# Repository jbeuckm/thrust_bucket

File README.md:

## Atmega328 test stand for rocket motors.

Based on the ["Ultra Simple Bucket Stand"](http://aeroconsystems.com/cart/test-stand-pictorial)

* Rotary Encoder + button + LCD interface
* reads HX711 interface for load cell tracking at 80hz
* writes force readings to SD card
* beeper to signal countdown
* FET to light the igniter

2/19/17 Motor holder bolted on

2/9/17 Status: Loadcell Mounted on I-Beam

### Dependencies

LCD library:
[https://github.com/adafruit/Adafruit-RGB-LCD-Shield-Library](https://github.com/adafruit/Adafruit-RGB-LCD-Shield-Library)

HX711:
[https://github.com/bogde/HX711](https://github.com/bogde/HX711)

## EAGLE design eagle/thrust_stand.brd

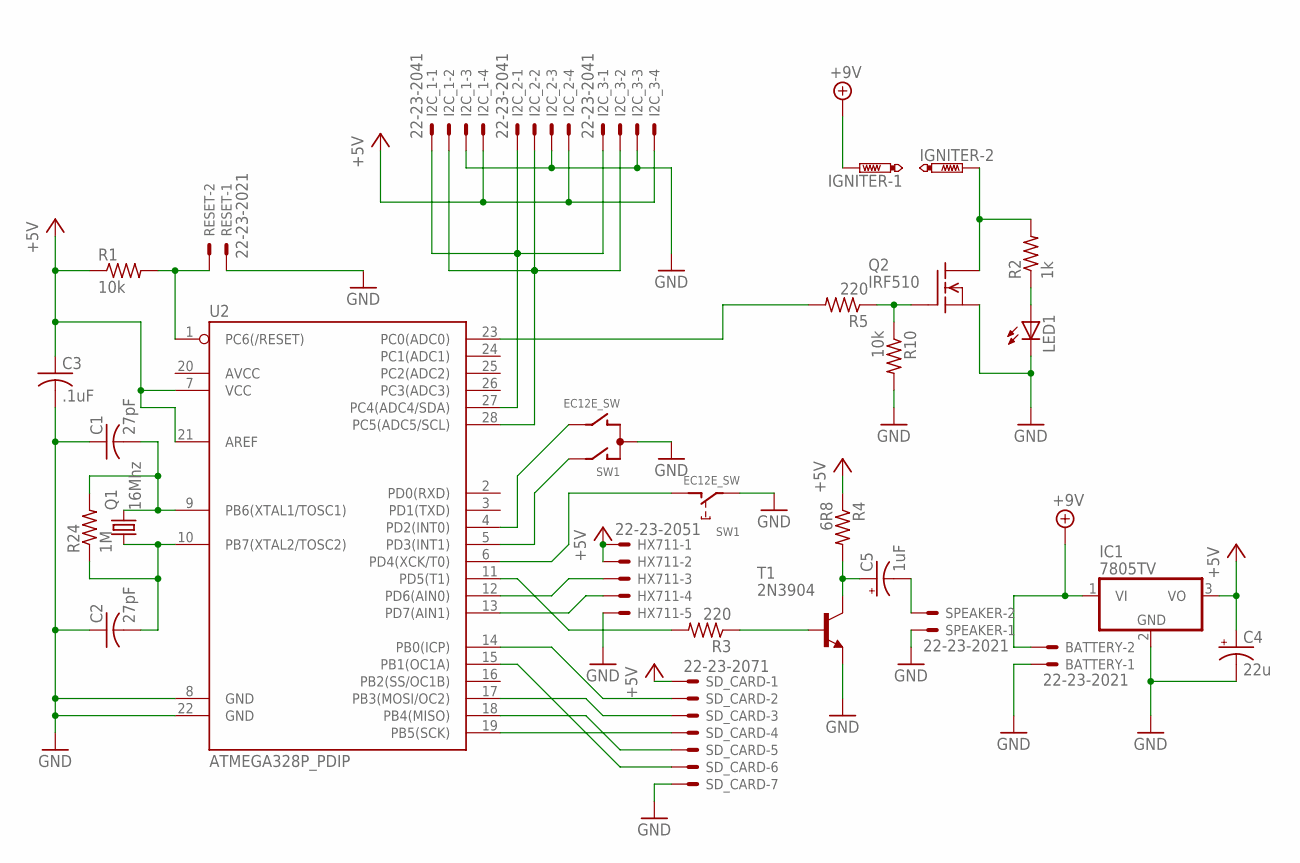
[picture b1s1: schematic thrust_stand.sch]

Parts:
BATTERY: 22-23-2021
C1, C2: 27pF; C025-040X050
C3: .1uF; C025-030X050
C4: 22u; B45181A
C5: 1uF; B45181A
HX711: 22-23-2051
I2C_1, I2C_2, I2C_3: 22-23-2041
IC1: 7805TV; TO220V
IGNITER: PTR2; P2-38-17
LED1: LED5MM
Q1: 16Mhz; HC49/S
Q2: IRF510; TO220
R1, R10: 10k; 0207/7
R2: 1k; 0207/7
R3: 220; 0207/7
R4: 6R8; 0207/7
R5: 220; 0309/10
R24: 1M; 0207/7
RESET: 22-23-2021
SD_CARD: 22-23-2071
SPEAKER: 22-23-2021
SW1: EC12E_SW; ALPS_EC12E_SW
T1: 2N3904; TO92
U2: ATMEGA328P_PDIP; DIL28-3

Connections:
+5V: C3.1, C4.+, HX711.1, HX711.2, I2C_1.4, I2C_2.4, I2C_3.4, IC1.3 (VO), R1.1, R4.1, SD_CARD.1, U2.7 (VCC), U2.21 (AREF)
+9V: BATTERY.2, IC1.1 (VI), IGNITER.TP-1
GND: BATTERY.1, C1.1, C2.1, C3.2, C4.-, HX711.5, I2C_1.3, I2C_2.3, I2C_3.3, IC1.2 (GND), LED1.K (C), Q2.3 (S), R10.2, RESET.1, SD_CARD.7, SPEAKER.1, SW1.C, SW1.E (2), T1.3 (E), U2.8 (GND), U2.22 (GND)
unnamed: I2C_1.2, I2C_2.2, I2C_3.2, U2.28 (PC5(ADC5/SCL))
unnamed: I2C_1.1, I2C_2.1, I2C_3.1, U2.27 (PC4(ADC4/SDA))
unnamed: HX711.3, U2.12 (PD6(AIN0))
unnamed: C1.2, Q1.2, R24.2, U2.9 (PB6(XTAL1/TOSC1))
unnamed: C2.2, Q1.1, R24.1, U2.10 (PB7(XTAL2/TOSC2))
unnamed: HX711.4, U2.13 (PD7(AIN1))
unnamed: SD_CARD.2, U2.14 (PB0(ICP))
unnamed: SD_CARD.3, U2.17 (PB3(MOSI/OC2))
unnamed: SD_CARD.4, U2.19 (PB5(SCK))
unnamed: SD_CARD.5, U2.18 (PB4(MISO))
unnamed: SD_CARD.6, U2.15 (PB1(OC1A))
unnamed: Q2.1 (G), R5.1, R10.1
unnamed: R3.2, U2.11 (PD5(T1))
unnamed: R3.1, T1.2 (B)
unnamed: C5.+, R4.2, T1.1 (C)
unnamed: C5.-, SPEAKER.2
unnamed: IGNITER.TP-2, Q2.2 (D), R2.2
unnamed: R5.2, U2.23 (PC0(ADC0))
unnamed: SW1.B, U2.4 (PD2(INT0))
unnamed: SW1.A, U2.5 (PD3(INT1))
unnamed: LED1.A, R2.1
unnamed: SW1.D (1), U2.6 (PD4(XCK/T0))
unnamed: R1.2, RESET.2, U2.1 (PC6(/RESET))

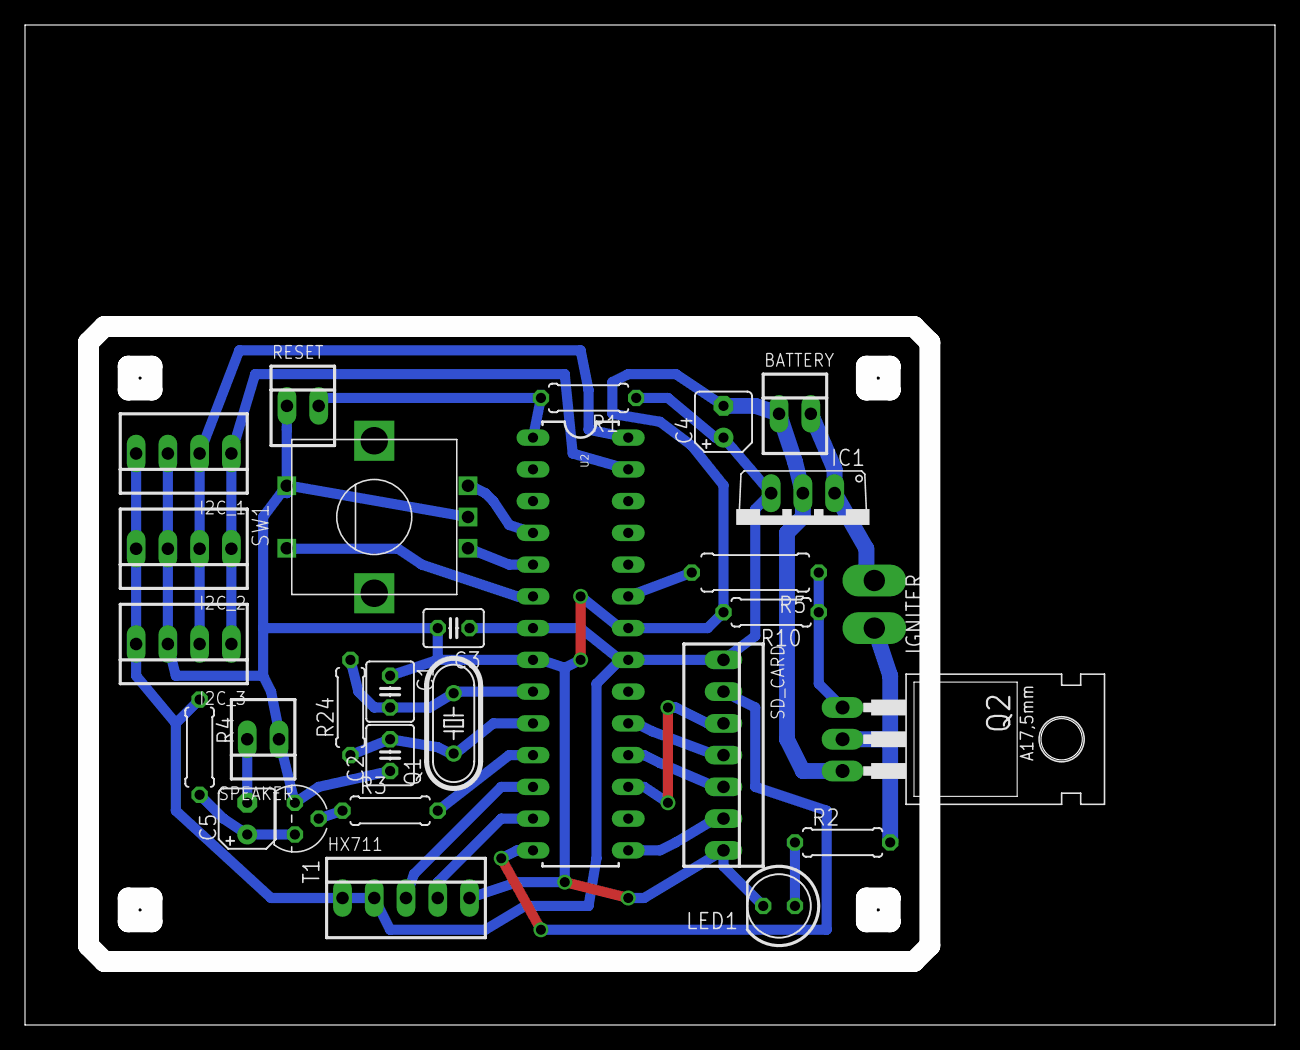
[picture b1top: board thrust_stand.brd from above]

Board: 2 copper layers, 100.0 x 80.0 mm, 28 parts (0 on the bottom side), 26 nets.

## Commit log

2017-01-16 small readme
2017-01-16 sd into readme
2017-01-17 added SD card and LCD code
2017-01-18 added hx711 to schemo
2017-01-18 added speaker to schemo
2017-01-18 state machine to light the igniter and save the data
2017-01-18 parts placed
2017-01-18 tweaks
2017-01-19 larger header for igniter
2017-01-20 routed
2017-01-26 fixed breaks for each case in loop switch
2017-02-04 measuring time between hx711 reads
2017-02-05 rotary encoder schemo and codes
2017-02-05 routed with cutout
2017-02-05 gcode for pcb
2017-02-06 spacer for load cell
2017-02-08 starting to try rotary encoder
2017-02-08 encoder working and hx711 reading
2017-02-09 scrolling through function names for calibration
2017-02-09 scrolling mode functions into class
2017-02-09 renaming to thrust_bucket
2017-02-09 built an interface for modes
2017-02-09 photo
2017-02-09 readme updated
2017-02-09 base class for mode functions
2017-02-09 implementing first mode function
2017-02-09 functions are in a pointer array
2017-02-09 added a calibrate mode
2017-02-09 trying to load calibration factor from eeprom
2017-02-09 now using a mode pointer instead of switch
2017-02-10 printing function labels now but nan for reading
2017-02-10 hopefully saved good calib value to eeprom
2017-02-10 two functions available but switched hx711 read to counting for the moment - unknown problem reading could be hardware
2017-02-10 reading but always zero
2017-02-10 changed all objects to pointers
2017-02-10 moved trace strings to flash mem
2017-02-10 verified same address for pointer to scale
2017-02-11 constructor initializers were not running before derived constructors
2017-02-11 compiling as sloeber project
2017-02-11 Added advance mode function to move to next mode
2017-02-12 adding countdown ignite and cancel
2017-02-12 corrected constructor traces and cleanup
2017-02-12 returning int from update to indicate mode change request
2017-02-12 changemodefunction
2017-02-12 parametrized project path to build on different machine
2017-02-12 passing mode change request back to loop()
2017-02-12 passing modeChangeRequest back to top
2017-02-12 refactors and zeroing modechangerequests when mode starts
2017-02-12 fixed FIRE label
2017-02-12 reporting raw value from hx711
2017-02-13 corrected startMode ordering so function label shows
2017-02-13 test sequence works and records to sd card
2017-02-13 starting a graph for thrust measurements
2017-02-14 no serial reports for faster loop
2017-02-15 report filename and bytes written
2017-02-15 quick open close for size after flush and close
2017-02-15 displaying impulse
2017-02-15 finding next free filename and reporting written file and size
2017-02-19 better calibration sequence and motor holder CAM
2017-02-19 motor holder pic
2017-02-22 igniter moved to supply side and saving calibration value when finished calib
2017-02-23 select element with latest test file selected
2017-02-25 coloring motor class scales
2017-02-25 showing motor classes
2017-03-02 holder cap
2017-03-06 wider legs on base and bigger holes in cap
2017-03-07 start and end times
2017-03-07 thrust in Ns
2017-03-07 showing avg thrust
2017-03-07 showing burn time
2017-03-29 copying data results with test names

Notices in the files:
parts and their libraries:
SparkFun-DigitalIC: Licensing: Creative Commons ShareAlike 4.0 International - https://creativecommons.org/licenses/by-sa/4.0
